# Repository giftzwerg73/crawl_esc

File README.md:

Kicad design files for simple crawler esc running am32 firmware

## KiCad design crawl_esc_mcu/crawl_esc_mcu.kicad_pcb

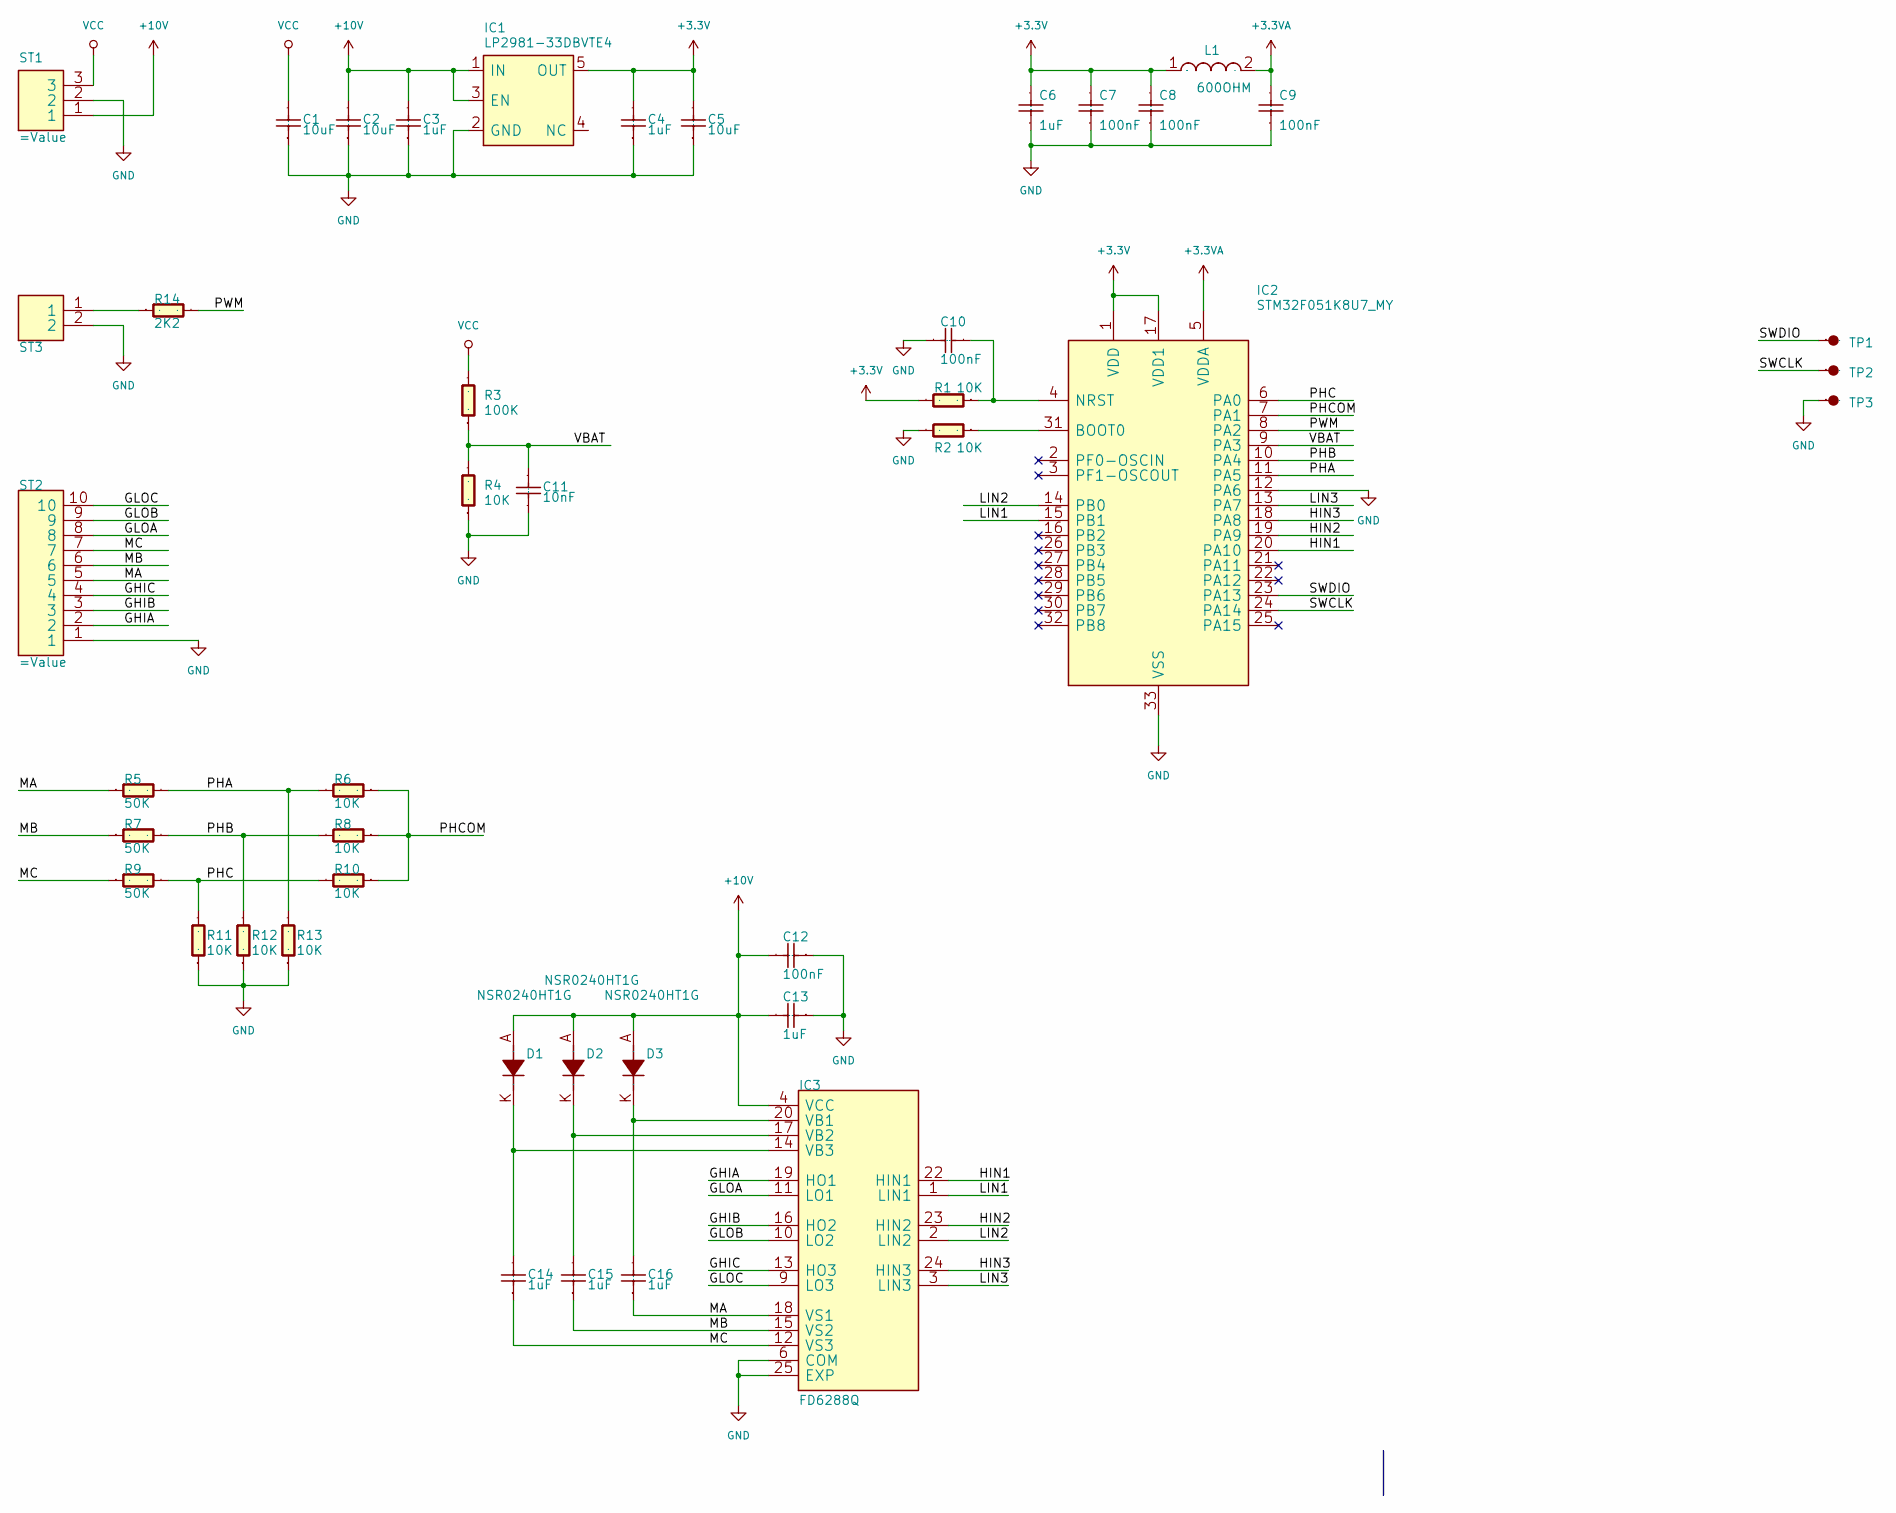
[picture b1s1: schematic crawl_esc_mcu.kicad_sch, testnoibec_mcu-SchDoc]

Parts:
C1, C2, C5: 10uF
C3, C4, C6, C13, C14, C15, C16: 1uF
C7, C8, C9, C10, C12: 100nF
C11: 10nF
D1, D2, D3: NSR0240HT1G
IC1: LP2981-33DBVTE4
IC2: STM32F051K8U7_MY
IC3: FD6288Q
L1: 600OHM
R1, R2, R4, R6, R8, R10, R11, R12, R13: 10K
R3: 100K
R5, R7, R9: 50K
R14: 2K2
ST1, ST2: =Value
ST3: (no value)
TP1, TP2, TP3: (no value)

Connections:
+3.3VA: C9.2, IC2.5 (VDDA), L1.2
+3V3: C4.2, C5.2, C6.2, C7.2, C8.2, IC1.5 (OUT), IC2.1 (VDD), IC2.17 (VDD1), L1.1, R1.2
+10V: C2.2, C3.2, C12.2, C13.2, D1.A, D2.A, D3.A, IC1.1 (IN), IC1.3 (EN), IC3.4 (VCC), ST1.1
/GHIA: IC3.19 (HO1), ST2.2
/GHIB: IC3.16 (HO2), ST2.3
/GHIC: IC3.13 (HO3), ST2.4
/GLOA: IC3.11 (LO1), ST2.8
/GLOB: IC3.10 (LO2), ST2.9
/GLOC: IC3.9 (LO3), ST2.10
/HIN1: IC2.20 (PA10), IC3.22 (HIN1)
/HIN2: IC2.19 (PA9), IC3.23 (HIN2)
/HIN3: IC2.18 (PA8), IC3.24 (HIN3)
/LIN1: IC2.15 (PB1), IC3.1 (LIN1)
/LIN2: IC2.14 (PB0), IC3.2 (LIN2)
/LIN3: IC2.13 (PA7), IC3.3 (LIN3)
/MA: C16.1, IC3.18 (VS1), R5.1, ST2.5
/MB: C15.1, IC3.15 (VS2), R7.1, ST2.6
/MC: C14.1, IC3.12 (VS3), R9.1, ST2.7
/PHA: IC2.11 (PA5), R5.2, R6.2, R13.2
/PHB: IC2.10 (PA4), R7.2, R8.2, R12.2
/PHC: IC2.6 (PA0), R9.2, R10.2, R11.2
/PHCOM: IC2.7 (PA1), R6.1, R8.1, R10.1
/PWM: IC2.8 (PA2), R14.2
/SWCLK: IC2.24 (PA14), TP2.1
/SWDIO: IC2.23 (PA13), TP1.1
/VBAT: C11.2, IC2.9 (PA3), R3.1, R4.2
GND: C1.1, C2.1, C3.1, C4.1, C5.1, C6.1, C7.1, C8.1, C9.1, C10.2, C11.1, C12.1, C13.1, IC1.2 (GND), IC2.12 (PA6), IC2.33 (VSS), IC3.6 (COM), IC3.25 (EXP), R2.2, R4.1, R11.1, R12.1, R13.1, ST1.2, ST2.1, ST3.2, TP3.1
unnamed: C10.1, IC2.4 (NRST), R1.1
unnamed: C14.2, D1.K, IC3.14 (VB3)
unnamed: C15.2, D2.K, IC3.17 (VB2)
unnamed: C16.2, D3.K, IC3.20 (VB1)
unnamed: IC2.31 (BOOT0), R2.1
unnamed: R14.1, ST3.1
VCC: C1.2, R3.2, ST1.3

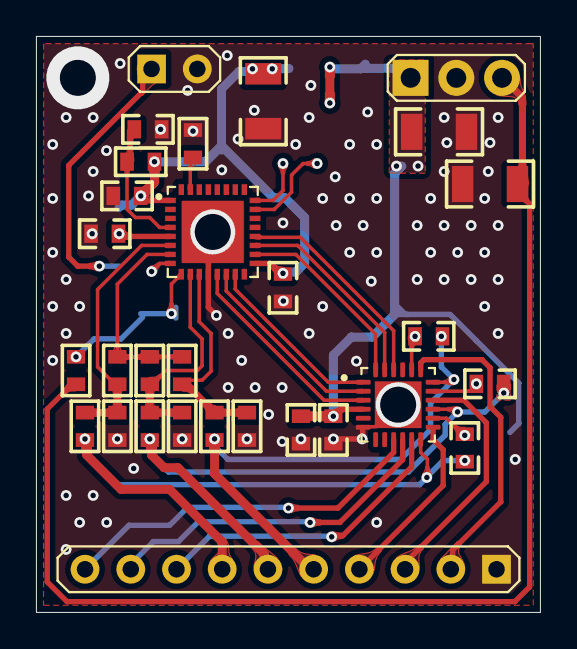
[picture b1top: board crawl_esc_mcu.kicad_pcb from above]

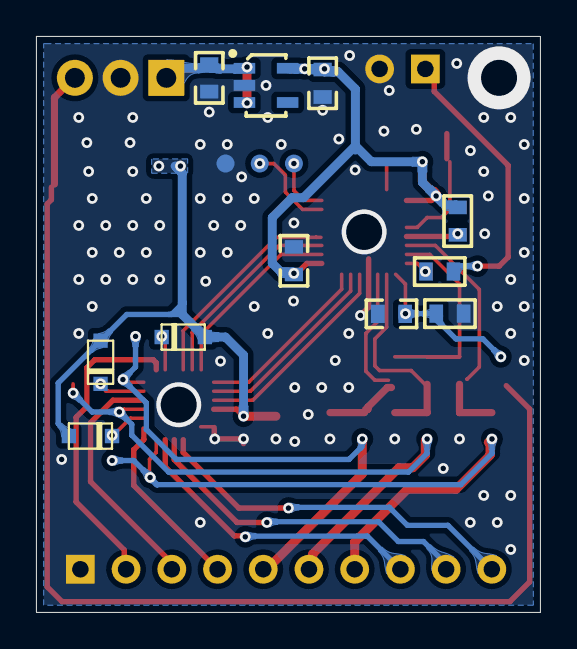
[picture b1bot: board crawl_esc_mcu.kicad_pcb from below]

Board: 2 copper layers, 28.0 x 32.0 mm, 43 parts (11 on the bottom side), 34 nets.

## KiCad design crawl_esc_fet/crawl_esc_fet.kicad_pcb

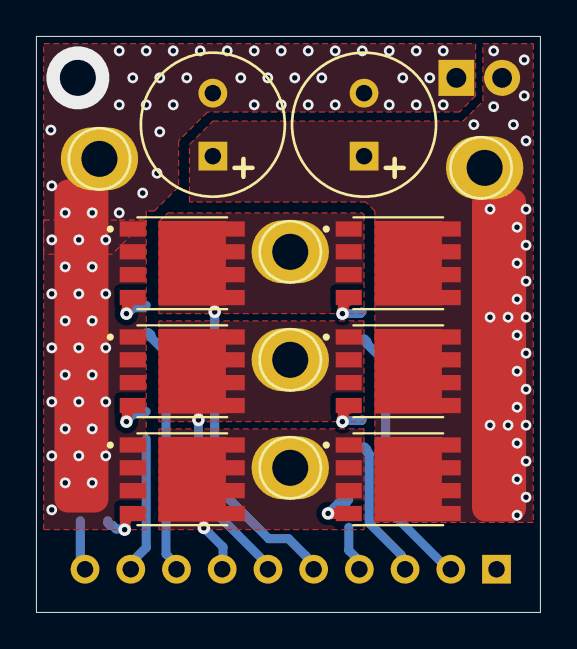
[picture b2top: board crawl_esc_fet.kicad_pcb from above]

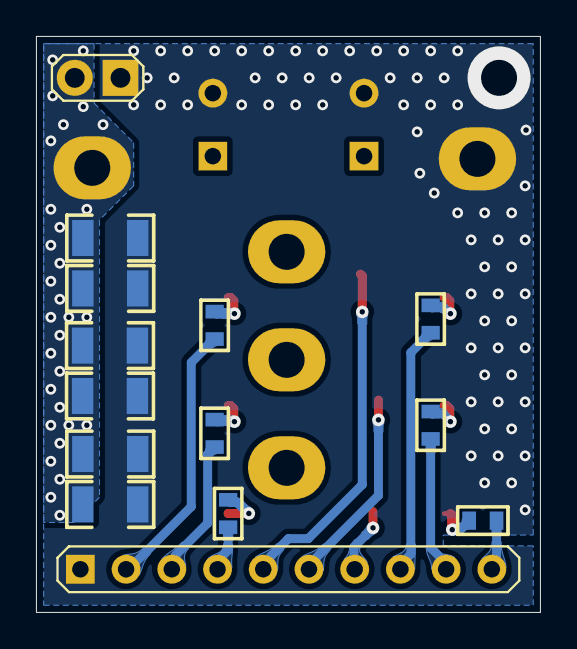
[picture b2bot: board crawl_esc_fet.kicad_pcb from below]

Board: 2 copper layers, 28.0 x 32.0 mm, 27 parts (14 on the bottom side), 17 nets.

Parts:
C1, C2: 220uF; CAP+_D8_3R5
C3, C4, C5, C6, C7, C8: 10uF; C1206
Q1, Q3, Q5, Q7, Q9, Q11: TPHR8504PL,L1Q; TRANS_TPHR8504PL,L1Q
R1, R2, R3, R4, R5, R6: 10R; R0603
ST1: STL2X1
ST2: =Value; STL10X1
TP1, TP2, TP3, TP4, TP5: WIRE_TH_PAD

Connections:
/GHIA: R3.1, ST2.2
/GHIB: R2.1, ST2.3
/GHIC: R1.1, ST2.4
/GLOA: R6.1, ST2.8
/GLOB: R5.1, ST2.9
/GLOC: R4.1, ST2.10
/MA: Q5.1 (S), Q5.2 (S), Q5.3 (S), Q11.5 (D), Q11.6 (D), Q11.7 (D), Q11.8 (D), Q11.9 (D), ST2.5, TP5.1
/MB: Q3.1 (S), Q3.2 (S), Q3.3 (S), Q9.5 (D), Q9.6 (D), Q9.7 (D), Q9.8 (D), Q9.9 (D), ST2.6, TP4.1
/MC: Q1.1 (S), Q1.2 (S), Q1.3 (S), Q7.5 (D), Q7.6 (D), Q7.7 (D), Q7.8 (D), Q7.9 (D), ST2.7, TP3.1
GND: C1.2, C2.2, C3.1, C4.1, C5.1, C6.1, C7.1, C8.1, Q7.1 (S), Q7.2 (S), Q7.3 (S), Q9.1 (S), Q9.2 (S), Q9.3 (S), Q11.1 (S), Q11.2 (S), Q11.3 (S), ST1.1, ST2.1, TP2.1
unnamed: Q1.4 (G), R1.2
unnamed: Q3.4 (G), R2.2
unnamed: Q5.4 (G), R3.2
unnamed: Q7.4 (G), R4.2
unnamed: Q9.4 (G), R5.2
unnamed: Q11.4 (G), R6.2
VCC: C1.1, C2.1, C3.2, C4.2, C5.2, C6.2, C7.2, C8.2, Q1.5 (D), Q1.6 (D), Q1.7 (D), Q1.8 (D), Q1.9 (D), Q3.5 (D), Q3.6 (D), Q3.7 (D), Q3.8 (D), Q3.9 (D), Q5.5 (D), Q5.6 (D), Q5.7 (D), Q5.8 (D), Q5.9 (D), ST1.2, TP1.1

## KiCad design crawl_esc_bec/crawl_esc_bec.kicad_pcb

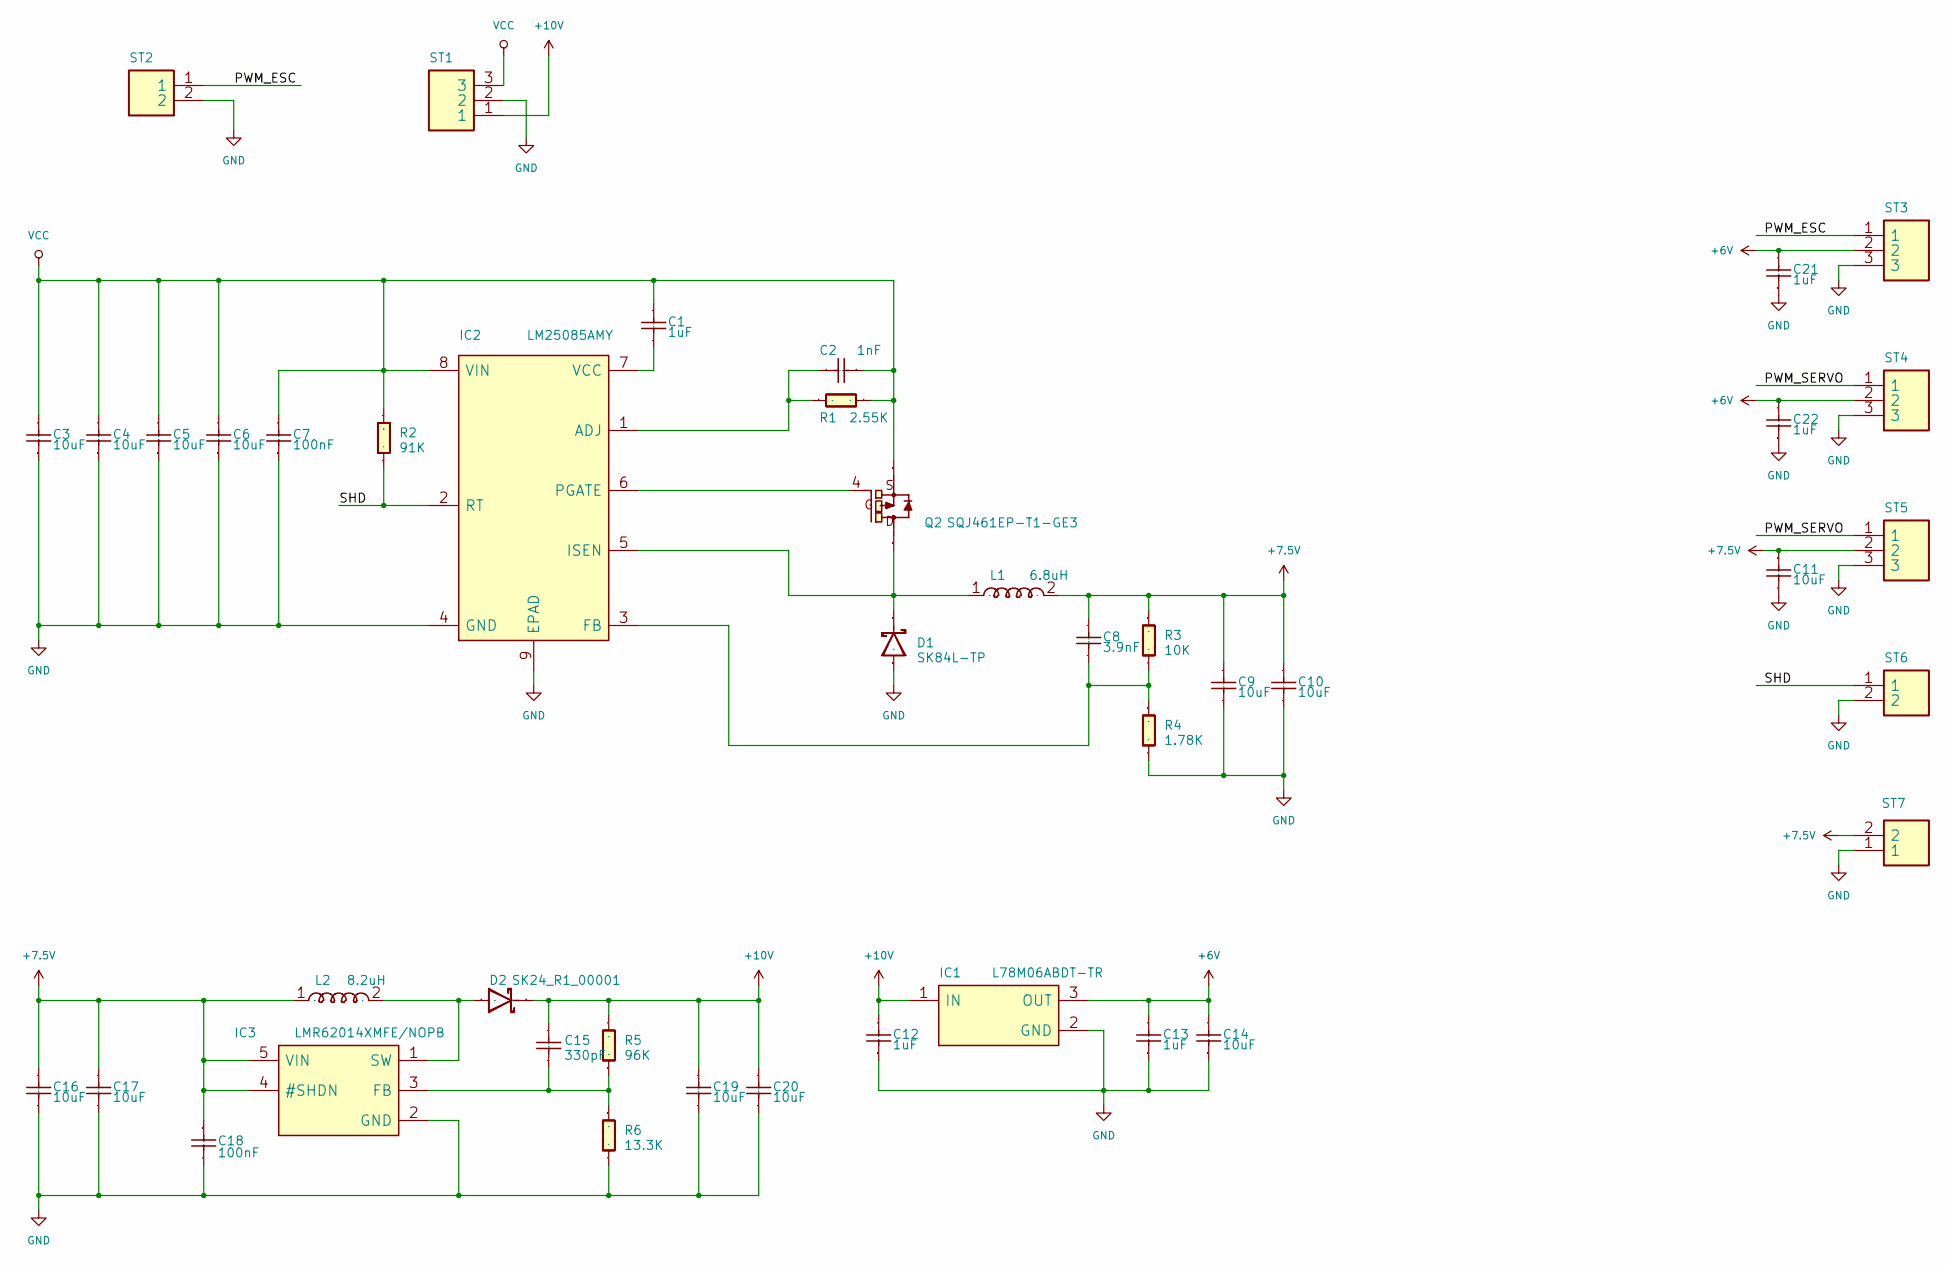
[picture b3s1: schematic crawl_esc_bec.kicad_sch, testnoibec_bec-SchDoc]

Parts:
C1, C12, C13, C21, C22: 1uF
C2: 1nF
C3, C4, C5, C6, C9, C10, C11, C14, C16, C17, C19, C20: 10uF
C7, C18: 100nF
C8: 3.9nF
C15: 330pF
D1: SK84L-TP
D2: SK24_R1_00001
IC1: L78M06ABDT-TR
IC2: LM25085AMY
IC3: LMR62014XMFE/NOPB
L1: 6.8uH
L2: 8.2uH
Q2: SQJ461EP-T1-GE3
R1: 2.55K
R2: 91K
R3: 10K
R4: 1.78K
R5: 96K
R6: 13.3K
ST1: =Value; STL3X1
ST2, ST6, ST7: STL2X1
ST3, ST4: =Value
ST5: (no value)

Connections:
+6V: C13.2, C14.2, C21.2, C22.2, IC1.3 (OUT), ST3.2, ST4.2
+7.5V: C8.2, C9.2, C10.2, C11.1, C16.2, C17.2, C18.1, IC3.4 (#SHDN), IC3.5 (VIN), L1.2, L2.1, R3.1, ST5.2, ST7.2
+10V: C12.2, C15.2, C19.2, C20.2, D2.K, IC1.1 (IN), R5.2, ST1.1
/PWM_ESC: ST2.1, ST3.1
/PWM_SERVO: ST4.1, ST5.1
/SHD: IC2.2 (RT), R2.2, ST6.1
GND: C3.1, C4.1, C5.1, C6.1, C7.1, C9.1, C10.1, C11.2, C12.1, C13.1, C14.1, C16.1, C17.1, C18.2, C19.1, C20.1, C21.1, C22.1, D1.A, IC1.2 (GND), IC2.4 (GND), IC2.9 (EPAD), IC3.2 (GND), R4.2, R6.2, ST1.2, ST2.2, ST3.3, ST4.3, ST5.3, ST6.2, ST7.1
unnamed: C1.1, IC2.7 (VCC)
unnamed: C2.2, IC2.1 (ADJ), R1.1
unnamed: C8.1, IC2.3 (FB), R3.2, R4.1
unnamed: C15.1, IC3.3 (FB), R5.1, R6.1
unnamed: D1.K, IC2.5 (ISEN), L1.1, Q2.5 (D), Q2.6 (D), Q2.7 (D), Q2.8 (D), Q2.9 (D)
unnamed: D2.A, IC3.1 (SW), L2.2
unnamed: IC2.6 (PGATE), Q2.4 (G)
VCC: C1.2, C2.1, C3.2, C4.2, C5.2, C6.2, C7.2, IC2.8 (VIN), Q2.1 (S), Q2.2 (S), Q2.3 (S), R1.2, R2.1, ST1.3

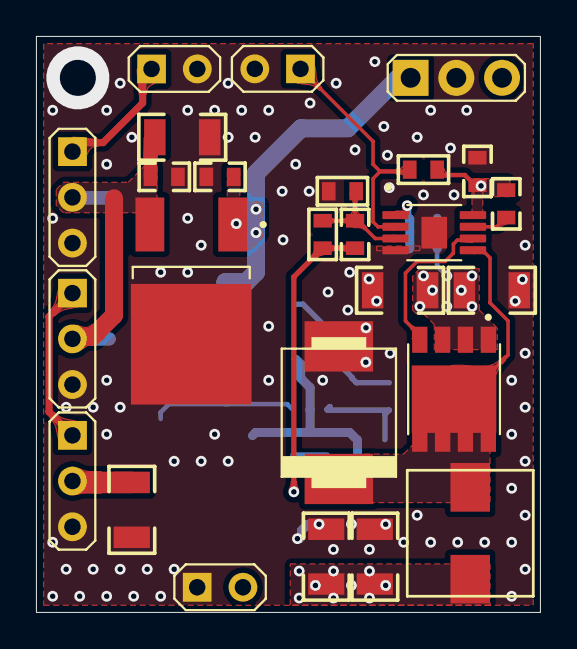
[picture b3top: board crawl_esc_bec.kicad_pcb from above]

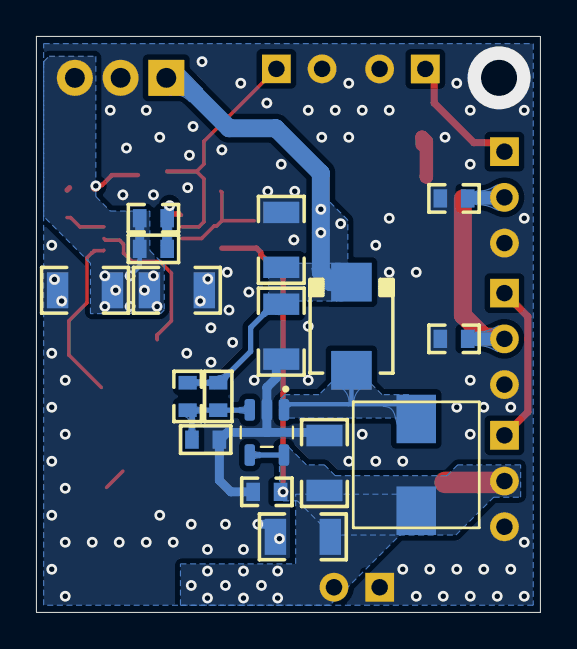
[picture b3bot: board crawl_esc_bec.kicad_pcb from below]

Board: 2 copper layers, 28.0 x 32.0 mm, 43 parts (17 on the bottom side), 15 nets.

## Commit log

2022-04-24 change stepup isens layout
2022-04-24 add readme
2022-04-25 edit readme
